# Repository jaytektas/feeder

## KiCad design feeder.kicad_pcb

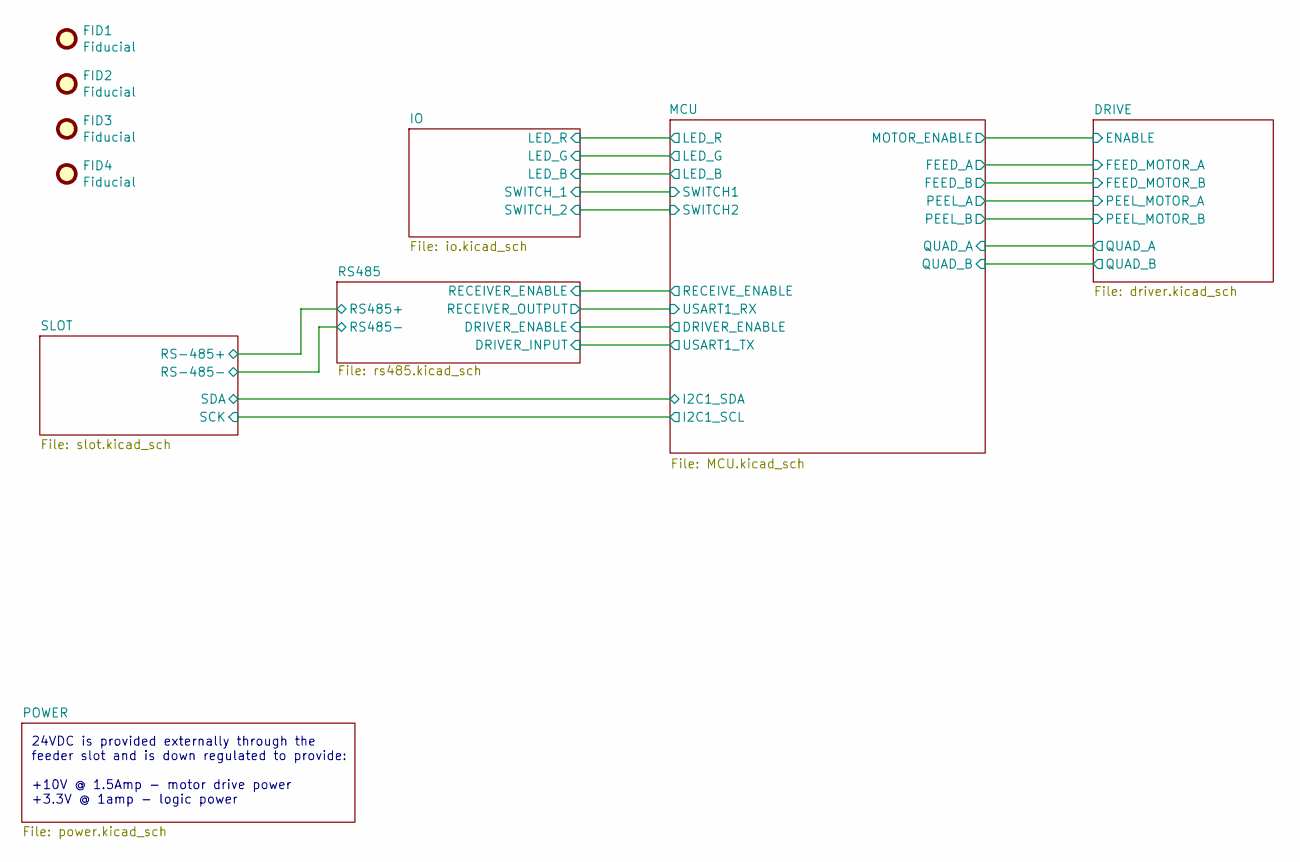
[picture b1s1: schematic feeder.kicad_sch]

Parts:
FID1, FID2, FID3, FID4: Fiducial; Fiducial_1mm_Mask2mm

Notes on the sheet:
24VDC is provided externally through the feeder slot and is down regulated to provide: +10V @ 1.5Amp - motor drive power +3.3V @ 1amp - logic power

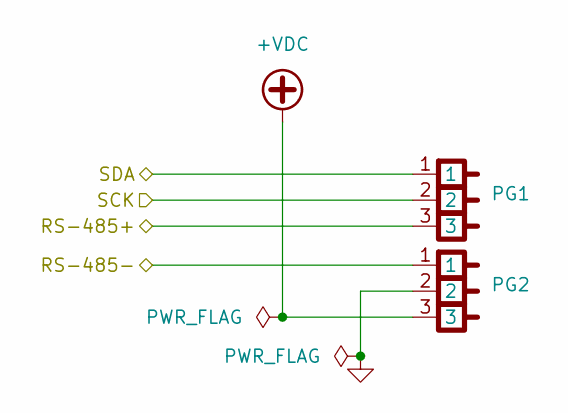
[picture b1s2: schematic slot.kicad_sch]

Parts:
PG1, PG2: POGO_3

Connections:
+VDC: PG2.3; also elsewhere on the board
/MCU/I2C1_SCL: PG1.2; also elsewhere on the board
/MCU/I2C1_SDA: PG1.1; also elsewhere on the board
/RS485/RS485+: PG1.3; also elsewhere on the board
/RS485/RS485-: PG2.1; also elsewhere on the board
GND: PG2.2; also elsewhere on the board

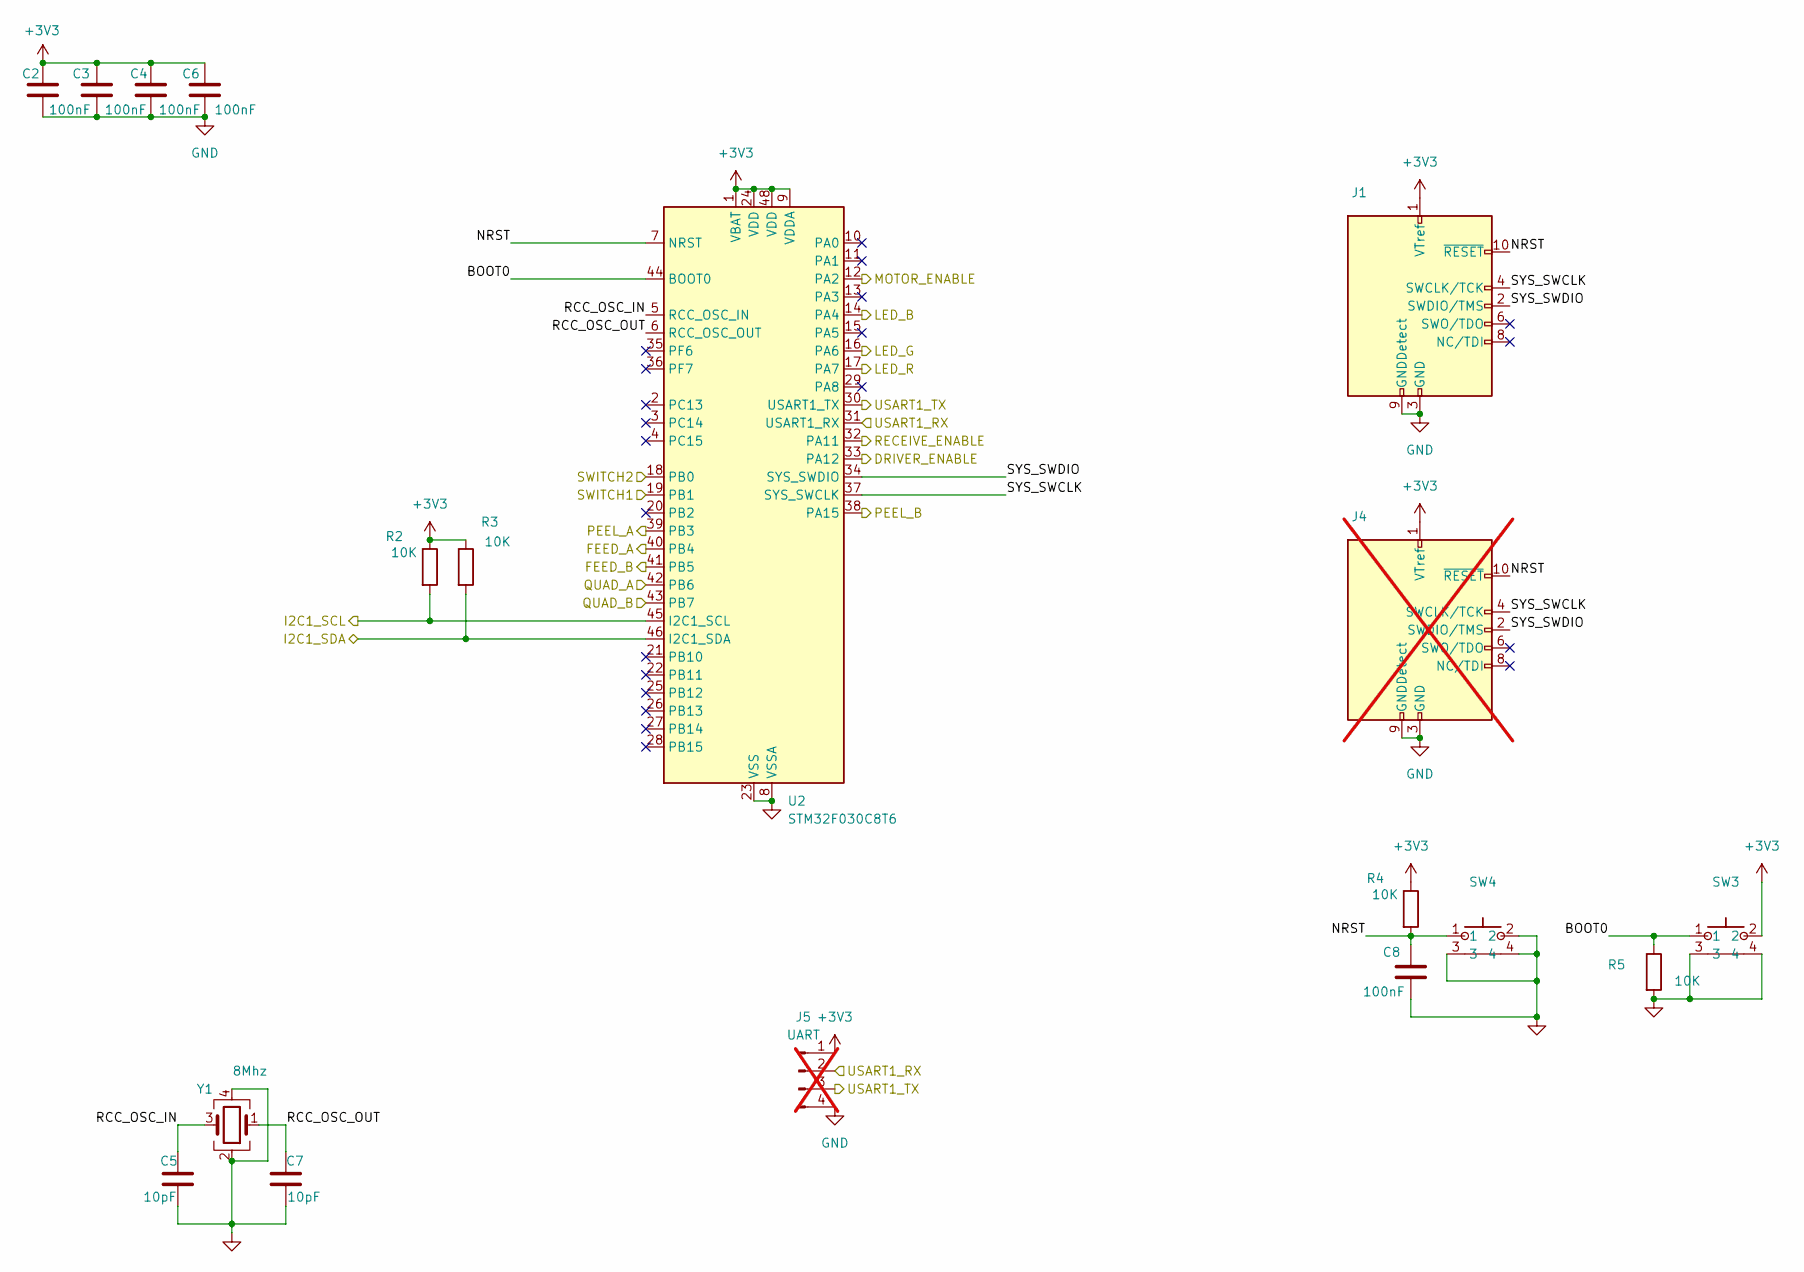
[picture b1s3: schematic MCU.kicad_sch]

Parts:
C2, C3, C4, C6, C8: 100nF; C_0603_1608Metric; LCSC C14663
C5, C7: 10pF; C_0603_1608Metric; LCSC C1634
J1: Conn_ARM_JTAG_SWD_10; PinHeader_2x05_P1.27mm_Vertical_SMD; LCSC C6332249
J4: Conn_ARM_JTAG_SWD_10; PinHeader_2x05_P1.27mm_Vertical_SMD; LCSC C6332249; not fitted
J5: UART; PinHeader_1x04_P2.54mm_Vertical; LCSC C2691448; not fitted
R2, R3, R4, R5: 10K; R_0603_1608Metric; LCSC C25804
SW3, SW4: 1TS003B-1400-3500A-CT; LCSC C319392
U2: STM32F030C8T6; LQFP-48_7x7mm_P0.5mm; LCSC C23922
Y1: 8Mhz; Crystal_SMD_3225-4Pin_3.2x2.5mm; LCSC C648984

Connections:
+3V3: C2.1, C3.1, C4.1, C6.1, J1.1 (VTref), J4.1 (VTref), J5.1, R2.1, R3.1, R4.1, SW3.2, U2.1 (VBAT), U2.9 (VDDA), U2.24 (VDD), U2.48 (VDD); also elsewhere on the board
/DRIVE/ENABLE: U2.12 (PA2); also elsewhere on the board
/DRIVE/FEED_MOTOR_A: U2.40 (PB4); also elsewhere on the board
/DRIVE/FEED_MOTOR_B: U2.41 (PB5); also elsewhere on the board
/DRIVE/PEEL_MOTOR_A: U2.39 (PB3); also elsewhere on the board
/DRIVE/PEEL_MOTOR_B: U2.38 (PA15); also elsewhere on the board
/DRIVE/QUAD_A: U2.42 (PB6); also elsewhere on the board
/DRIVE/QUAD_B: U2.43 (PB7); also elsewhere on the board
/IO/LED_B: U2.14 (PA4); also elsewhere on the board
/IO/LED_G: U2.16 (PA6); also elsewhere on the board
/IO/LED_R: U2.17 (PA7); also elsewhere on the board
/IO/SWITCH_1: U2.19 (PB1); also elsewhere on the board
/IO/SWITCH_2: U2.18 (PB0); also elsewhere on the board
/MCU/BOOT0: R5.1, SW3.1, U2.44 (BOOT0)
/MCU/DRIVER_ENABLE: U2.33 (PA12); also elsewhere on the board
/MCU/I2C1_SCL: R2.2, U2.45 (I2C1_SCL); also elsewhere on the board
/MCU/I2C1_SDA: R3.2, U2.46 (I2C1_SDA); also elsewhere on the board
/MCU/NRST: C8.1, J1.10 (~RESET), J4.10 (~RESET), R4.2, SW4.1, U2.7 (NRST)
/MCU/RCC_OSC_IN: C5.2, U2.5 (RCC_OSC_IN), Y1.3
/MCU/RCC_OSC_OUT: C7.2, U2.6 (RCC_OSC_OUT), Y1.1
/MCU/RECEIVE_ENABLE: U2.32 (PA11); also elsewhere on the board
/MCU/SYS_SWCLK: J1.4 (SWCLK/TCK), J4.4 (SWCLK/TCK), U2.37 (SYS_SWCLK)
/MCU/SYS_SWDIO: J1.2 (SWDIO/TMS), J4.2 (SWDIO/TMS), U2.34 (SYS_SWDIO)
/MCU/USART1_RX: J5.2, U2.31 (USART1_RX); also elsewhere on the board
/MCU/USART1_TX: J5.3, U2.30 (USART1_TX); also elsewhere on the board
GND: C2.2, C3.2, C4.2, C5.1, C6.2, C7.1, C8.2, J1.3 (GND), J1.5 (GND), J1.9 (GNDDetect), J4.3 (GND), J4.5 (GND), J4.9 (GNDDetect), J5.4, R5.2, SW3.3, SW3.4, SW4.2, SW4.3, SW4.4, U2.8 (VSSA), U2.23 (VSS), U2.47 (VSS), Y1.2, Y1.4; also elsewhere on the board

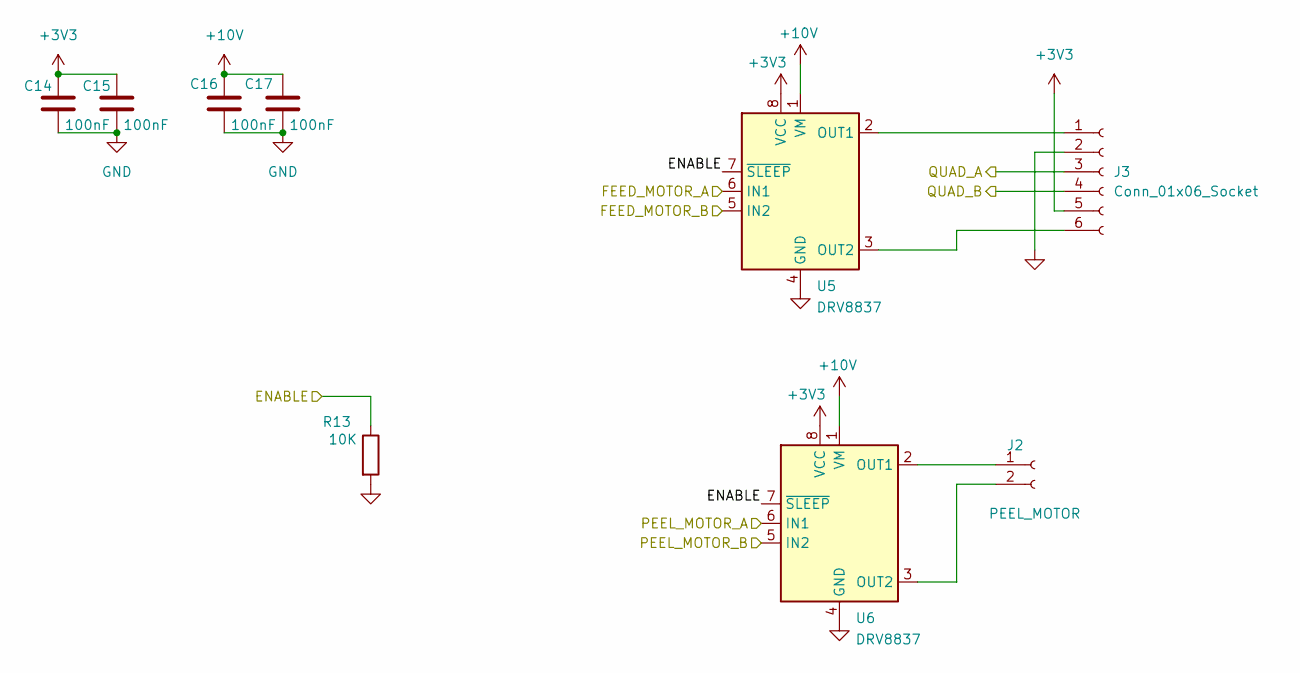
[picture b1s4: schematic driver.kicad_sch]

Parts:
C14, C15, C16, C17: 100nF; C_0603_1608Metric; LCSC C14663
J2: PEEL_MOTOR; Molex_PicoBlade_53261-0271_1x02-1MP_P1.25mm_Horizontal; LCSC C2845379
J3: Conn_01x06_Socket; Molex_PicoBlade_53261-0671_1x06-1MP_P1.25mm_Horizontal; LCSC C2845383
R13: 10K; R_0603_1608Metric; LCSC C25804
U5, U6: DRV8837; WSON-8-1EP_2x2mm_P0.5mm_EP0.9x1.6mm; LCSC C191000

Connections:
+3V3: C14.1, C15.1, J3.5, U5.8 (VCC), U6.8 (VCC); also elsewhere on the board
+10V: C16.1, C17.1, U5.1 (VM), U6.1 (VM); also elsewhere on the board
/DRIVE/ENABLE: R13.1, U5.7 (~SLEEP), U6.7 (~SLEEP); also elsewhere on the board
/DRIVE/FEED_MOTOR_A: U5.6 (IN1); also elsewhere on the board
/DRIVE/FEED_MOTOR_B: U5.5 (IN2); also elsewhere on the board
/DRIVE/PEEL_MOTOR_A: U6.6 (IN1); also elsewhere on the board
/DRIVE/PEEL_MOTOR_B: U6.5 (IN2); also elsewhere on the board
/DRIVE/QUAD_A: J3.3; also elsewhere on the board
/DRIVE/QUAD_B: J3.4; also elsewhere on the board
GND: C14.2, C15.2, C16.2, C17.2, J3.2, R13.2, U5.4 (GND), U5.9 (GND), U6.4 (GND), U6.9 (GND); also elsewhere on the board
unnamed: J2.1, U6.2 (OUT1)
unnamed: J2.2, U6.3 (OUT2)
unnamed: J3.1, U5.2 (OUT1)
unnamed: J3.6, U5.3 (OUT2)

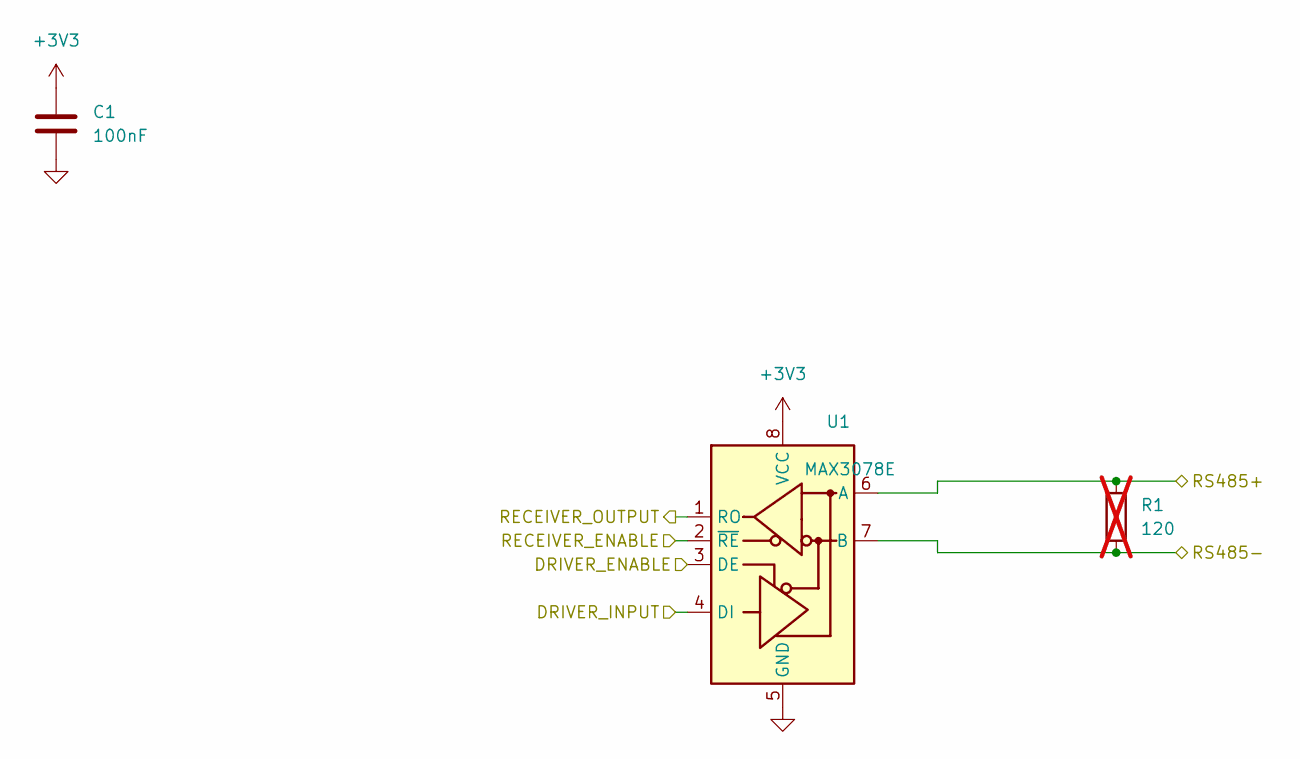
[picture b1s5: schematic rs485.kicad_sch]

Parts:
C1: 100nF; C_0603_1608Metric; LCSC C14663
R1: 120; R_0603_1608Metric; not fitted
U1: MAX3078E; SOIC-8_3.9x4.9mm_P1.27mm; LCSC C2885450

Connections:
+3V3: C1.1, U1.8 (VCC); also elsewhere on the board
/MCU/DRIVER_ENABLE: U1.3 (DE); also elsewhere on the board
/MCU/RECEIVE_ENABLE: U1.2 (~RE); also elsewhere on the board
/MCU/USART1_RX: U1.1 (RO); also elsewhere on the board
/MCU/USART1_TX: U1.4 (DI); also elsewhere on the board
/RS485/RS485+: R1.1, U1.6 (A); also elsewhere on the board
/RS485/RS485-: R1.2, U1.7 (B); also elsewhere on the board
GND: C1.2, U1.5 (GND); also elsewhere on the board

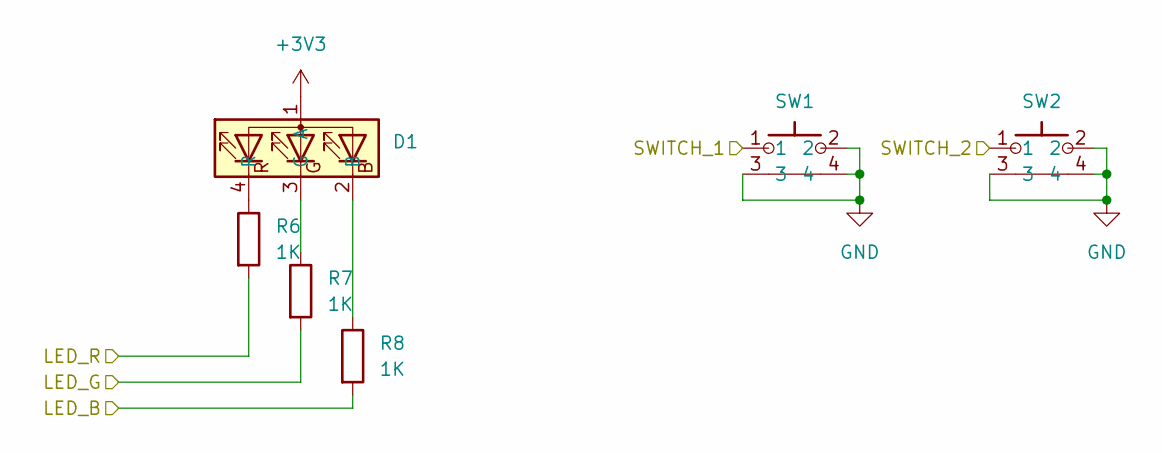
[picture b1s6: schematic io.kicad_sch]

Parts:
D1: MHS110FRGBCT; LCSC C496820
R6, R7, R8: 1K; R_0603_1608Metric; LCSC C21190
SW1, SW2: 1TS003B-1400-3500A-CT; LCSC C319392

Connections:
+3V3: D1.1 (A); also elsewhere on the board
/IO/LED_B: R8.2; also elsewhere on the board
/IO/LED_G: R7.2; also elsewhere on the board
/IO/LED_R: R6.2; also elsewhere on the board
/IO/SWITCH_1: SW1.1; also elsewhere on the board
/IO/SWITCH_2: SW2.1; also elsewhere on the board
GND: SW1.2, SW1.3, SW1.4, SW2.2, SW2.3, SW2.4; also elsewhere on the board
unnamed: D1.2 (B), R8.1
unnamed: D1.3 (G), R7.1
unnamed: D1.4 (R), R6.1

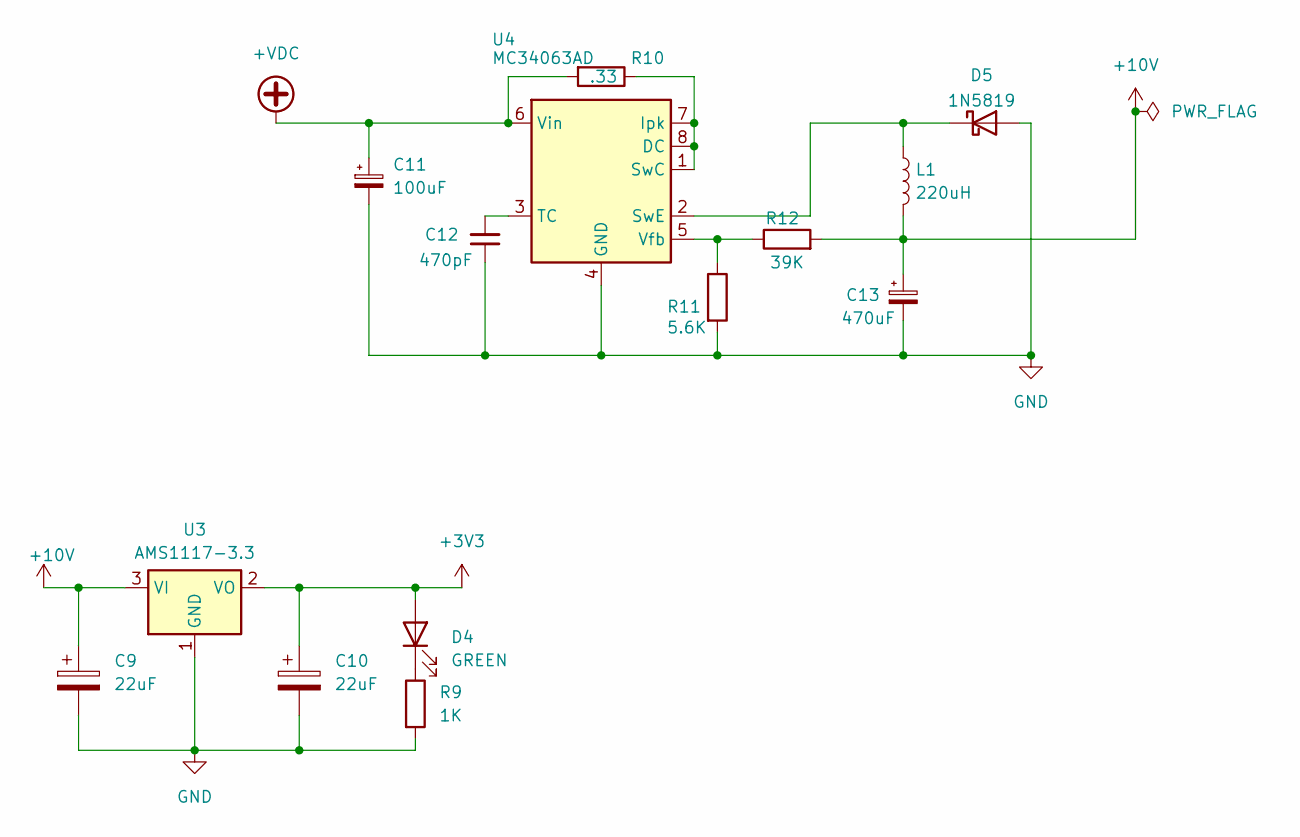
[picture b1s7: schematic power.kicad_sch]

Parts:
C9, C10: 22uF; C_1206_3216Metric; LCSC C7432785
C11: 100uF; C_Elec_6.3x7.7; LCSC C2836442
C12: 470pF; C_0603_1608Metric; LCSC C107092
C13: 470uF; C_Elec_6.3x7.7; LCSC C5354997
D4: GREEN; LED_0603_1608Metric; LCSC C965804
D5: 1N5819; D_SOD-123; LCSC C82544
L1: 220uH; SMNR6045; LCSC C467145
R9: 1K; R_0603_1608Metric; LCSC C21190
R10: .33; R_0805_2012Metric; LCSC C2934265
R11: 5.6K; R_0603_1608Metric; LCSC C114627
R12: 39K; R_0603_1608Metric; LCSC C163424
U3: AMS1117-3.3; SOT-223-3_TabPin2; LCSC C347222
U4: MC34063AD; SOIC-8_3.9x4.9mm_P1.27mm; LCSC C80213

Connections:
+3V3: C10.1, D4.2 (A), U3.2 (VO); also elsewhere on the board
+10V: C9.1, C13.1, L1.2, R12.2, U3.3 (VI); also elsewhere on the board
+VDC: C11.1, R10.2, U4.6 (Vin); also elsewhere on the board
GND: C9.2, C10.2, C11.2, C12.1, C13.2, D5.2 (A), R9.2, R11.2, U3.1 (GND), U4.4 (GND); also elsewhere on the board
unnamed: D4.1 (K), R9.1
unnamed: D5.1 (K), L1.1, U4.2 (SwE)
unnamed: R10.1, U4.1 (SwC), U4.7 (Ipk), U4.8 (DC)
unnamed: C12.2, U4.3 (TC)
unnamed: R11.1, R12.1, U4.5 (Vfb)

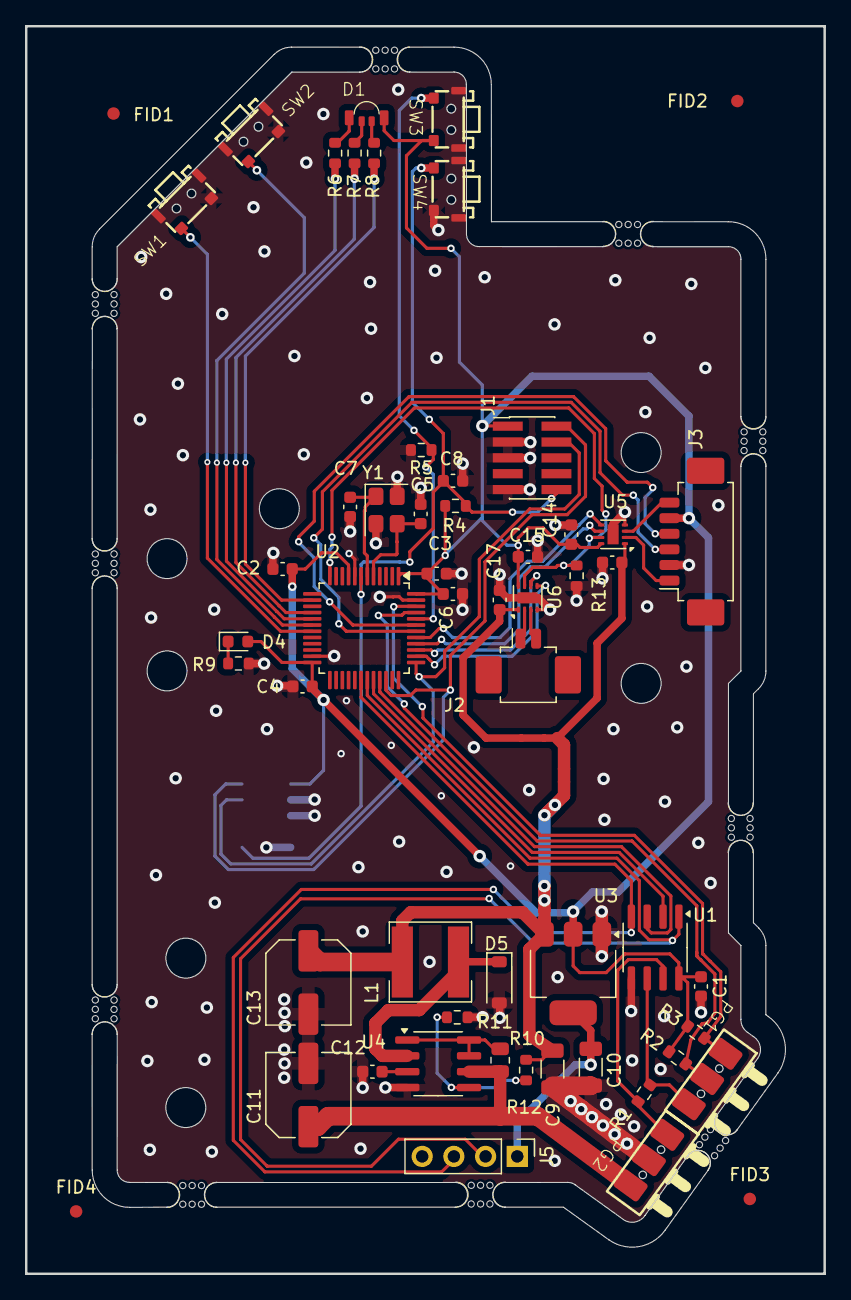
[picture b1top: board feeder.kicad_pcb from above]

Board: 2 copper layers, 64.0 x 100.0 mm, 66 parts (1 on the bottom side), 42 nets.

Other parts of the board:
mouse-bite-2mm-slot, mouse-bite-2mm-slot#2, mouse-bite-2mm-slot#3, mouse-bite-2mm-slot#4, mouse-bite-2mm-slot#5, mouse-bite-2mm-slot#6, mouse-bite-2mm-slot#7, mouse-bite-2mm-slot#8, mouse-bite-2mm-slot#9, mouse-bite-2mm-slot#10: VAL**; mouse-bite-2mm-slot

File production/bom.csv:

Designator,Footprint,Quantity,Value,LCSC Part #
"C1, C14, C15, C16, C17, C2, C3, C4, C6, C8",0603,10,100nF,C14663
"C10, C9",1206,2,22uF,C7432785
C11,C_Elec_6.3x7.7,1,100uF,C2836442
C12,0603,1,470pF,C107092
C13,C_Elec_6.3x7.7,1,470uF,C5354997
"C5, C7",0603,2,10pF,C1634
D1,MHS110FRGBCT,1,~,C496820
D4,0603,1,GREEN,C965804
D5,D_SOD-123,1,1N5819,C82544
J1,PinHeader_2x05_P1.27mm_Vertical_SMD,1,Conn_ARM_JTAG_SWD_10,C6332249
J2,Molex_PicoBlade_53261-0271_1x02-1MP_P1.25mm_Horizontal,1,PEEL_MOTOR,C2845379
J3,Molex_PicoBlade_53261-0671_1x06-1MP_P1.25mm_Horizontal,1,Conn_01x06_Socket,C2845383
L1,SMNR6045,1,220uH,C467145
"MOUSE-BITE-2MM-SLOT_10, MOUSE-BITE-2MM-SLOT_9, MOUSE-BITE-2MM-SLOT_8, MOUSE-BITE-2MM-SLOT_7, MOUSE-BITE-2MM-SLOT_6, MOUSE-BITE-2MM-SLOT_5, MOUSE-BITE-2MM-SLOT_4, MOUSE-BITE-2MM-SLOT_3, MOUSE-BITE-2MM-SLOT_2, MOUSE-BITE-2MM-SLOT",mouse-bite-2mm-slot,10,VAL**,
R10,0805,1,.33,C2934265
R11,0603,1,5.6K,C114627
R12,0603,1,39K,C163424
"R13, R2, R3, R4, R5",0603,5,10K,C25804
"R6, R7, R8, R9",0603,4,1K,C21190
"SW1, SW2, SW3, SW4",1TS003B-1400-3500A-CT,4,~,
U1,SOIC-8_3.9x4.9mm_P1.27mm,1,MAX3078E,C2885450
U2,LQFP-48_7x7mm_P0.5mm,1,STM32F031C6T6,C97413
U3,SOT-223-3_TabPin2,1,AMS1117-3.3,C347222
U4,SOIC-8_3.9x4.9mm_P1.27mm,1,MC34063AD,C80213
"U5, U6",WSON-8-1EP_2x2mm_P0.5mm_EP0.9x1.6mm,2,DRV8837,C191000
Y1,Crystal_SMD_3225-4Pin_3.2x2.5mm,1,8Mhz,C648984

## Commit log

2025-06-05 feeder pcb files
2025-06-05 clean up
2025-06-22 updated part sizes for pick and place
2025-06-22 imported schematic fields to pcb for placement
